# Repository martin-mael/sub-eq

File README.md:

# Sub EQ

Égaliseur graphique 5 bandes pour caissons de basses (31, 40, 50, 63, 80 Hz), mono, jacks 6,35 mm, alimentation 12 V DC. Exemplaire unique, PCB 90 × 62 mm, boîtier 97 × 71 × 25 mm.

| Document | Contenu |
|---|---|
| [docs/SPEC.md](docs/SPEC.md) | spécification validée et valeurs figées à la conception |
| [docs/sub-eq-fiche.pdf](docs/sub-eq-fiche.pdf) | fiche de présentation : schéma fonctionnel, courbes, carte, nomenclature, coût |
| [docs/BOM.md](docs/BOM.md) | nomenclature détaillée de tous les composants |
| [docs/COMMANDE.md](docs/COMMANDE.md) | PCB, composants, visserie à commander |
| [docs/CHIFFRAGE.md](docs/CHIFFRAGE.md) | coût détaillé |
| [docs/MONTAGE.md](docs/MONTAGE.md) | contrôles, impression, soudure, tests, assemblage |
| [docs/ASSEMBLAGE-JLC.md](docs/ASSEMBLAGE-JLC.md) | option : CMS posés par JLCPCB, devis pour 2, 5 et 10 cartes |

## Fichiers produits

- `hardware/sub-eq.kicad_sch`, `hardware/sub-eq.kicad_pcb` : schéma et carte (générés, ne pas éditer à la main).
- `hardware/fab/` : Gerbers zippés, nomenclatures, PDF du schéma et de l'implantation, STEP de la carte.
- `hardware/sim-report.txt` : réponse calculée à partir des valeurs réelles du circuit.
- `enclosure/out/` : STL et STEP des 4 pièces imprimées, vue éclatée `preview.png`.
- `viewer/` : visionneuse 3D web (voir [viewer/README.md](viewer/README.md)).

| Domaine | Source | Généré |
|---|---|---|
| Visionneuse | `viewer/src/scene/dims.ts`, `Connectors.tsx` | `viewer/public/models/` via `npm run assets` |

Toute modification d'une pièce de panneau se répercute dans `hardware/scripts/gen_pcb.py`, `enclosure/enclosure.py` et `viewer/src/scene/dims.ts`.

## Régénérer

La fiche PDF et `docs/BOM.md` se régénèrent à part, après `build.sh` : `cd hardware/scripts && ../../.venv/bin/python build_doc.py` (il faut Google Chrome et `pypdf`).

```bash
FREEROUTING_JAR=~/.cache/freerouting/freerouting-2.5.0.jar ./build.sh
```

Il faut KiCad 10 dans `~/Applications/KiCad`, Java 21 ou plus, [Freerouting](https://github.com/freerouting/freerouting/releases) 2.5 et un `.venv` avec `numpy`, `build123d` et `cairosvg` (ici un lien vers celui d'audio-box).

Visionneuse 3D : `cd viewer && npm install && npm run assets && npm run dev` (http://localhost:5174).

## Déploiement de la visionneuse sur Vercel

Dans le projet Vercel, le **Root Directory** est `viewer` : Vercel y détecte Vite et lance `npm install`, `npm run build`, puis publie `dist`. `viewer/vercel.json` ne fait que fixer le framework. Les modèles 3D (`viewer/public/models/`) sont versionnés : Vercel n'a besoin ni de KiCad ni de Python. Relance `npm run assets` et commite avant de pousser si le PCB ou le boîtier a changé.

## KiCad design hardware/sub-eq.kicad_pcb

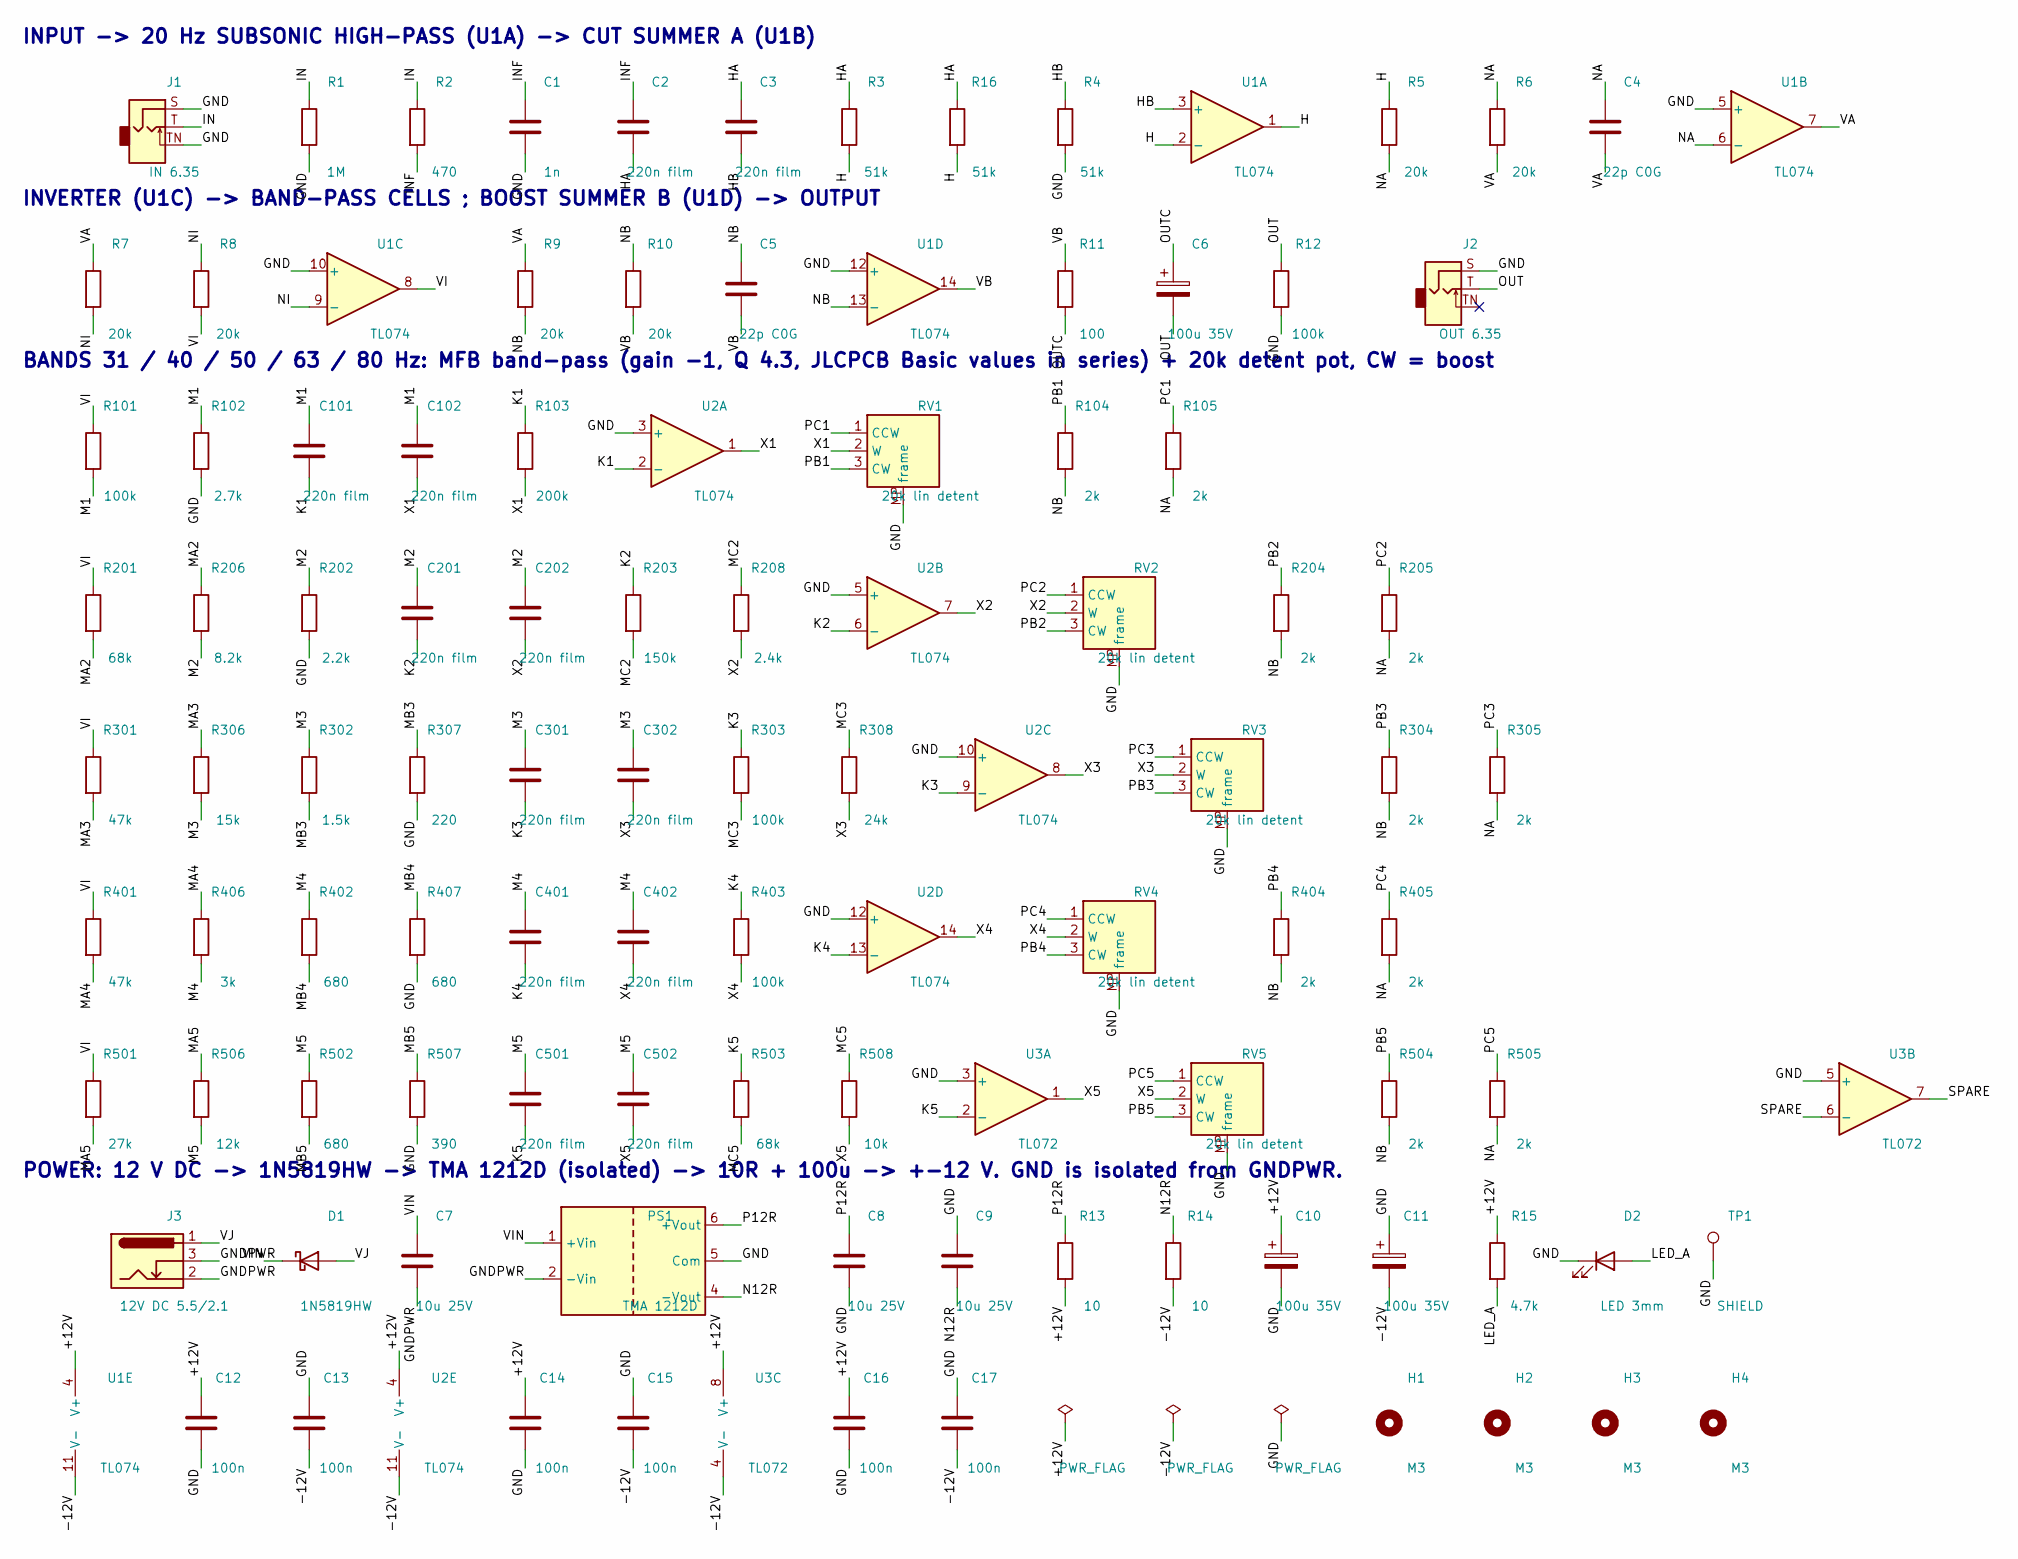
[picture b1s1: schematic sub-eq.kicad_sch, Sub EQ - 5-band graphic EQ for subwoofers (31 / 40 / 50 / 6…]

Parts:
C1: 1n; C_0805_2012Metric
C2, C3, C101, C102, C201, C202, C301, C302, C401, C402, C501, C502: 220n film; C_Rect_L7.2mm_W2.5mm_P5.00mm_FKS2_FKP2_MKS2_MKP2
C4, C5: 22p C0G; C_0805_2012Metric
C6, C10, C11: 100u 35V; CP_Elec_6.3x7.7
C7, C8, C9: 10u 25V; C_0805_2012Metric
C12, C13, C14, C15, C16, C17: 100n; C_0805_2012Metric
D1: 1N5819HW; D_SOD-123
D2: LED 3mm; LED_D3.0mm_Horizontal_O1.27mm_Z6.0mm
H1, H2, H3, H4: M3; MountingHole_3.2mm_M3
J1: IN 6.35; Jack_6.35mm_Neutrik_NMJ4HCD2_Horizontal
J2: OUT 6.35; Jack_6.35mm_Neutrik_NMJ4HCD2_Horizontal
J3: 12V DC 5.5/2.1; BarrelJack_CUI_PJ-102AH_Horizontal
PS1: TMA 1212D; Converter_DCDC_TRACO_TMA-05xxD_12xxD_Dual_THT
R1: 1M; R_0805_2012Metric
R2: 470; R_0805_2012Metric
R3, R4, R16: 51k; R_0805_2012Metric
R5, R6, R7, R8, R9, R10: 20k; R_0805_2012Metric
R11: 100; R_0805_2012Metric
R12, R101, R303, R403: 100k; R_0805_2012Metric
R13, R14: 10; R_0805_2012Metric
R15: 4.7k; R_0805_2012Metric
R102: 2.7k; R_0805_2012Metric
R103: 200k; R_0805_2012Metric
R104, R105, R204, R205, R304, R305, R404, R405, R504, R505: 2k; R_0805_2012Metric
R201, R503: 68k; R_0805_2012Metric
R202: 2.2k; R_0805_2012Metric
R203: 150k; R_0805_2012Metric
R206: 8.2k; R_0805_2012Metric
R208: 2.4k; R_0805_2012Metric
R301, R401: 47k; R_0805_2012Metric
R302: 1.5k; R_0805_2012Metric
R306: 15k; R_0805_2012Metric
R307: 220; R_0805_2012Metric
R308: 24k; R_0805_2012Metric
R402, R407, R502: 680; R_0805_2012Metric
R406: 3k; R_0805_2012Metric
R501: 27k; R_0805_2012Metric
R506: 12k; R_0805_2012Metric
R507: 390; R_0805_2012Metric
R508: 10k; R_0805_2012Metric
RV1, RV2, RV3, RV4, RV5: 20k lin detent; Potentiometer_Alps_RK09L_Single_Horizontal
TP1: SHIELD; TestPoint_THTPad_D2.5mm_Drill1.2mm
U1, U2: TL074; SOIC-14_3.9x8.7mm_P1.27mm
U3: TL072; SOIC-8_3.9x4.9mm_P1.27mm

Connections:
/+12V: C10.1, C12.1, C14.1, C16.1, R13.2, R15.1, U1.4 (V+), U2.4 (V+), U3.8 (V+)
/-12V: C11.2, C13.2, C15.2, C17.2, R14.2, U1.11 (V-), U2.11 (V-), U3.4 (V-)
/GND: C1.2, C8.2, C9.1, C10.2, C11.1, C12.2, C13.1, C14.2, C15.1, C16.2, C17.1, D2.1 (K), J1.S, J1.TN, J2.S, PS1.5 (Com), R1.2, R4.2, R12.2, R102.2, R202.2, R307.2, R407.2, R507.2, RV1.MP (frame), RV2.MP (frame), RV3.MP (frame), RV4.MP (frame), RV5.MP (frame), TP1.1, U1.5 (+), U1.10 (+), U1.12 (+), U2.3 (+), U2.5 (+), U2.10 (+), U2.12 (+), U3.3 (+), U3.5 (+)
/GNDPWR: C7.2, J3.2, J3.3, PS1.2 (-Vin)
/H: R3.2, R5.1, R16.2, U1.1, U1.2 (-)
/HA: C2.2, C3.1, R3.1, R16.1
/HB: C3.2, R4.1, U1.3 (+)
/IN: J1.T, R1.1, R2.1
/INF: C1.1, C2.1, R2.2
/K1: C101.2, R103.1, U2.2 (-)
/K2: C201.2, R203.1, U2.6 (-)
/K3: C301.2, R303.1, U2.9 (-)
/K4: C401.2, R403.1, U2.13 (-)
/K5: C501.2, R503.1, U3.2 (-)
/LED_A: D2.2 (A), R15.2
/M1: C101.1, C102.1, R101.2, R102.1
/M2: C201.1, C202.1, R202.1, R206.2
/M3: C301.1, C302.1, R302.1, R306.2
/M4: C401.1, C402.1, R402.1, R406.2
/M5: C501.1, C502.1, R502.1, R506.2
/MA2: R201.2, R206.1
/MA3: R301.2, R306.1
/MA4: R401.2, R406.1
/MA5: R501.2, R506.1
/MB3: R302.2, R307.1
/MB4: R402.2, R407.1
/MB5: R502.2, R507.1
/MC2: R203.2, R208.1
/MC3: R303.2, R308.1
/MC5: R503.2, R508.1
/N12R: C9.2, PS1.4 (-Vout), R14.1
/NA: C4.1, R5.2, R6.1, R105.2, R205.2, R305.2, R405.2, R505.2, U1.6 (-)
/NB: C5.1, R9.2, R10.1, R104.2, R204.2, R304.2, R404.2, R504.2, U1.13 (-)
/NI: R7.2, R8.1, U1.9 (-)
/OUT: C6.2, J2.T, R12.1
/OUTC: C6.1, R11.2
/P12R: C8.1, PS1.6 (+Vout), R13.1
/PB1: R104.1, RV1.3 (CW)
/PB2: R204.1, RV2.3 (CW)
/PB3: R304.1, RV3.3 (CW)
/PB4: R404.1, RV4.3 (CW)
/PB5: R504.1, RV5.3 (CW)
/PC1: R105.1, RV1.1 (CCW)
/PC2: R205.1, RV2.1 (CCW)
/PC3: R305.1, RV3.1 (CCW)
/PC4: R405.1, RV4.1 (CCW)
/PC5: R505.1, RV5.1 (CCW)
/SPARE: U3.6 (-), U3.7
/VA: C4.2, R6.2, R7.1, R9.1, U1.7
/VB: C5.2, R10.2, R11.1, U1.14
/VI: R8.2, R101.1, R201.1, R301.1, R401.1, R501.1, U1.8
/VIN: C7.1, D1.1 (K), PS1.1 (+Vin)
/VJ: D1.2 (A), J3.1
/X1: C102.2, R103.2, RV1.2 (W), U2.1
/X2: C202.2, R208.2, RV2.2 (W), U2.7
/X3: C302.2, R308.2, RV3.2 (W), U2.8
/X4: C402.2, R403.2, RV4.2 (W), U2.14
/X5: C502.2, R508.2, RV5.2 (W), U3.1

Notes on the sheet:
INPUT -> 20 Hz SUBSONIC HIGH-PASS (U1A) -> CUT SUMMER A (U1B)
INVERTER (U1C) -> BAND-PASS CELLS ; BOOST SUMMER B (U1D) -> OUTPUT
BANDS 31 / 40 / 50 / 63 / 80 Hz: MFB band-pass (gain -1, Q 4.3, JLCPCB Basic values in series) + 20k detent pot, CW = boost
POWER: 12 V DC -> 1N5819HW -> TMA 1212D (isolated) -> 10R + 100u -> +-12 V. GND is isolated from GNDPWR.

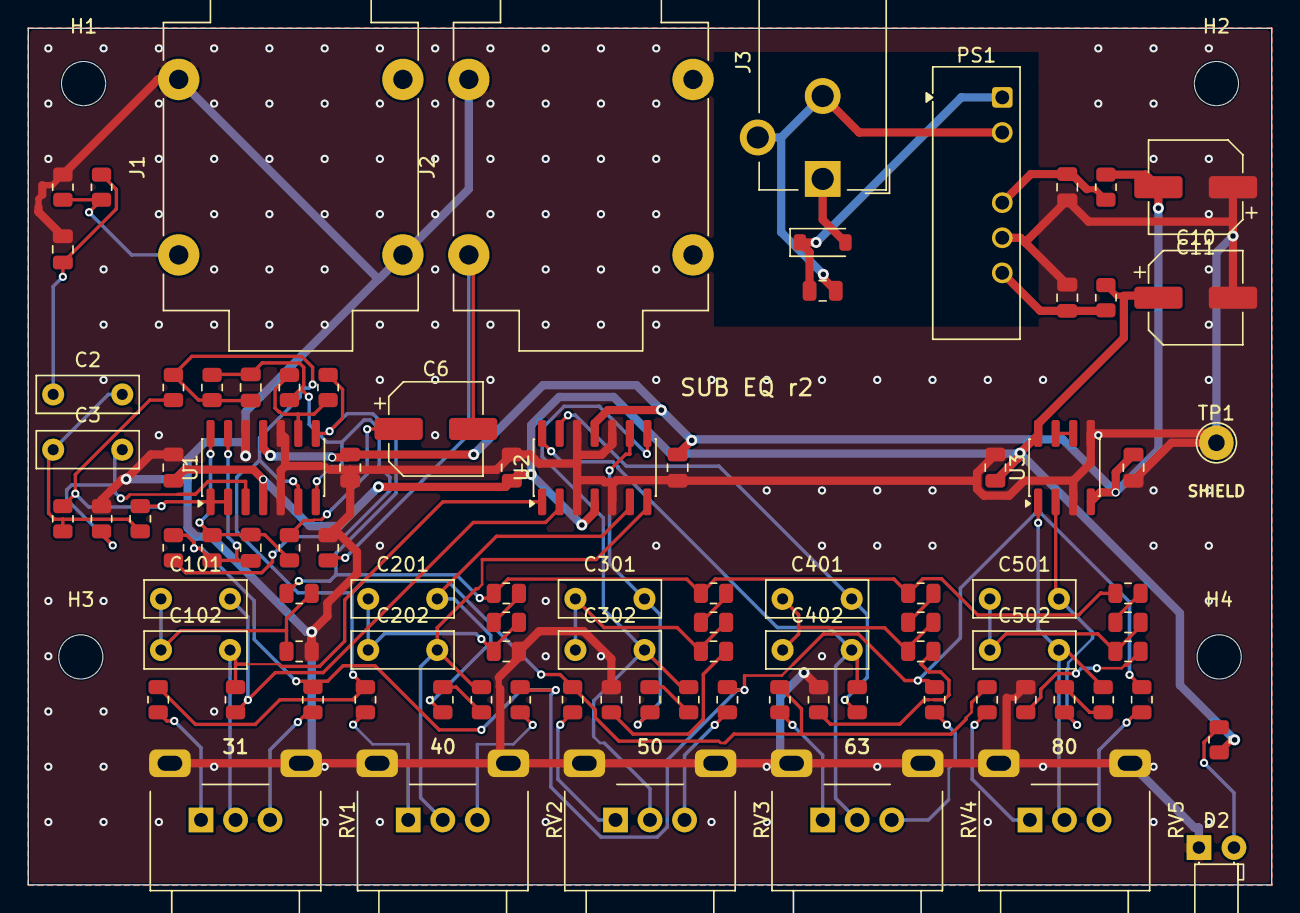
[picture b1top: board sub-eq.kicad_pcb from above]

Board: 2 copper layers, 90.0 x 62.0 mm, 97 parts (0 on the bottom side), 58 nets.

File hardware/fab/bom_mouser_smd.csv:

Manufacturer,Manufacturer Part Number,Quantity,Designators,Qty on board,Description
Yageo,CC0805JRNPO9BN102,10,C1,1,Cap 1nF 50V 0805 (C0G here; X7R is fine too)
Nichicon,UWT1V101MCL1GS,4,C10 C11 C6,3,Alu electrolytic 100uF 35V 6.3x7.7
Yageo,CC0805KRX7R9BB104,20,C12 C13 C14 C15 C16 C17,6,Cap 100nF 50V X7R 0805
Samsung,CL21C220JBANNNC,10,C4 C5,2,Cap 22pF 50V C0G 0805
Samsung,CL21A106KAYNNNG,10,C7 C8 C9,3,Cap 10uF 25V X5R 0805
Diodes Inc.,1N5819HW-7-F,2,D1,1,Schottky 40 V 1 A SOD-123 (reverse-polarity protection)
Yageo,RC0805FR-071ML,10,R1,1,Resistor 1M 1% 0805
Yageo,RC0805FR-0720KL,10,R10 R5 R6 R7 R8 R9,6,Resistor 20k 1% 0805
Yageo,RC0805FR-07100KL,10,R101 R12 R303 R403,4,Resistor 100k 1% 0805
Yageo,RC0805FR-072K7L,10,R102,1,Resistor 2.7k 1% 0805
Yageo,RC0805FR-07200KL,10,R103,1,Resistor 200k 1% 0805
Yageo,RC0805FR-072KL,10,R104 R105 R204 R205 R304 R305 R404 R405 R504 R505,10,Resistor 2k 1% 0805
Yageo,RC0805FR-07100RL,10,R11,1,Resistor 100 1% 0805
Yageo,RC0805FR-0710RL,10,R13 R14,2,Resistor 10 1% 0805
Yageo,RC0805FR-074K7L,10,R15,1,Resistor 4.7k 1% 0805
Yageo,RC0805FR-0751KL,10,R16 R3 R4,3,Resistor 51k 1% 0805
Yageo,RC0805FR-07470RL,10,R2,1,Resistor 470 1% 0805
Yageo,RC0805FR-0768KL,10,R201 R503,2,Resistor 68k 1% 0805
Yageo,RC0805FR-072K2L,10,R202,1,Resistor 2.2k 1% 0805
Yageo,RC0805FR-07150KL,10,R203,1,Resistor 150k 1% 0805
Yageo,RC0805FR-078K2L,10,R206,1,Resistor 8.2k 1% 0805
Yageo,RC0805FR-072K4L,10,R208,1,Resistor 2.4k 1% 0805
Yageo,RC0805FR-0747KL,10,R301 R401,2,Resistor 47k 1% 0805
Yageo,RC0805FR-071K5L,10,R302,1,Resistor 1.5k 1% 0805
Yageo,RC0805FR-0715KL,10,R306,1,Resistor 15k 1% 0805
Panasonic,ERJ-6ENF2200V,10,R307,1,Resistor 220 1% 0805 (Yageo out of stock)
Yageo,RC0805FR-0724KL,10,R308,1,Resistor 24k 1% 0805
Yageo,RC0805FR-07680RL,10,R402 R407 R502,3,Resistor 680 1% 0805
Yageo,RC0805FR-073KL,10,R406,1,Resistor 3k 1% 0805
Yageo,RC0805FR-0727KL,10,R501,1,Resistor 27k 1% 0805
Yageo,RC0805FR-0712KL,10,R506,1,Resistor 12k 1% 0805
Yageo,RC0805FR-07390RL,10,R507,1,Resistor 390 1% 0805
Yageo,RC0805FR-0710KL,10,R508,1,Resistor 10k 1% 0805
Texas Instruments,TL074CDR,2,U1 U2,2,Quad JFET op-amp SOIC-14
Texas Instruments,TL072CDR,1,U3,1,Dual JFET op-amp SOIC-8
